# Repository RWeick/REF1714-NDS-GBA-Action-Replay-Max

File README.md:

# REF1714-NDS-GBA-Action-Replay-Max
A full schematic, optimized PCB, and the rom dump. Be sure to use SLA Resin if you print the cartridge connector.

PCB Thickness: 0.8 mm

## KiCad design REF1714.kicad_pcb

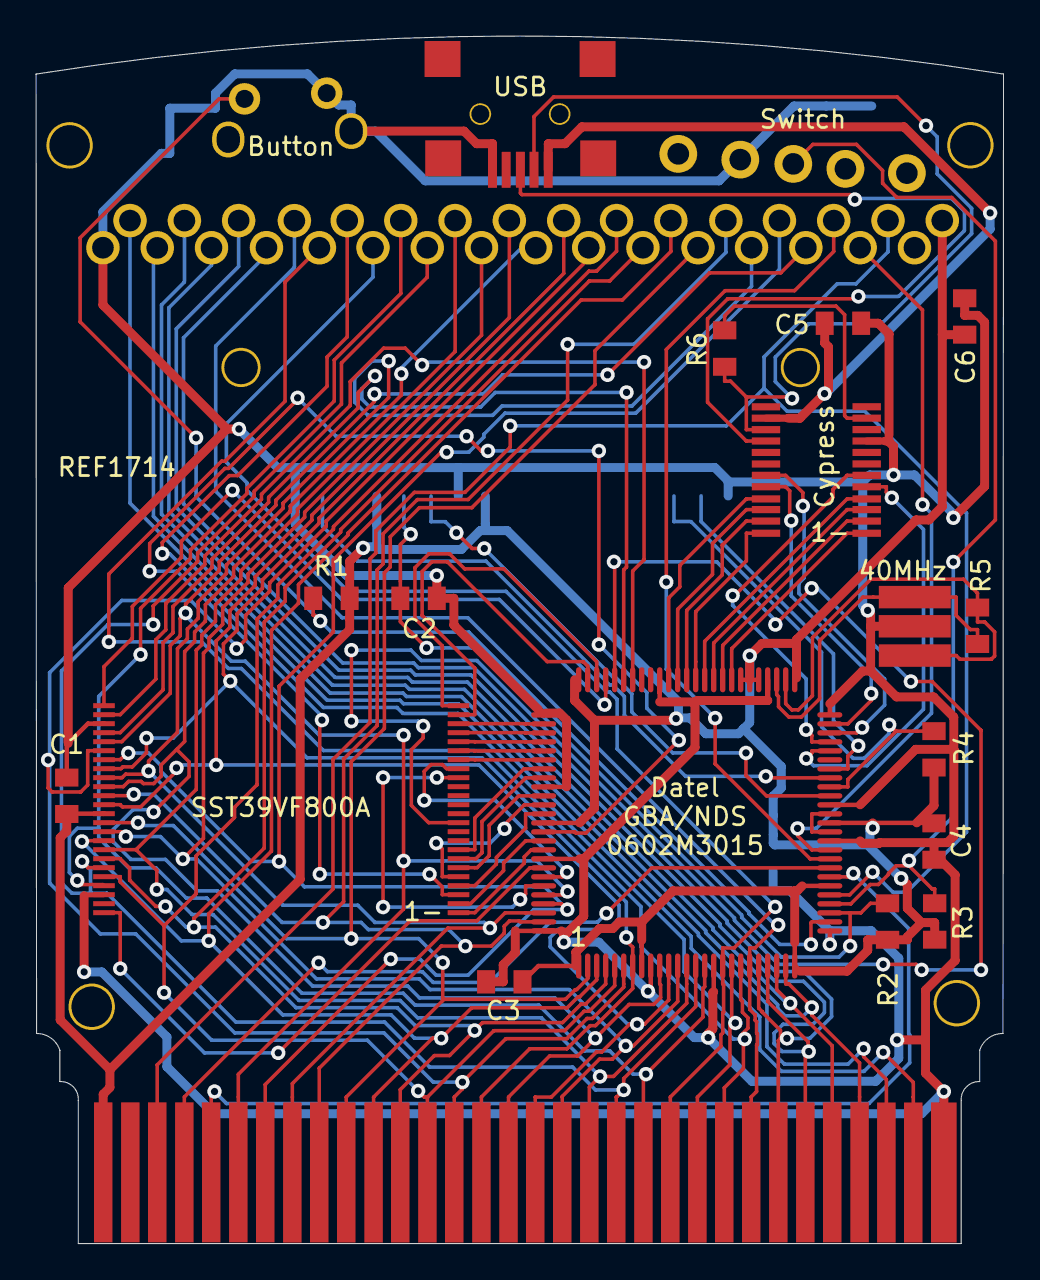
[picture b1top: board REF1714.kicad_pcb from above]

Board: 2 copper layers, 53.8 x 67.1 mm, 24 parts (0 on the bottom side), 81 nets.

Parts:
C1, C5: 400nF 0805; AR Max Capacitor
C2, C3, C4, C6: 100nF 0805; AR Max Capacitor
C7: Conn_01x03_Female; AR MAX Back Cap
DrillHoles: AR MAX Drill Holes
J1: USB_B_Mini; USB_Mini_B
J2: SW_DPDT_x2; Angled Switch
J3: System_Edge_Connector; Edge Connector
J4: Game_Edge_Connector; Cartridge Slot, GBC
R1, R2, R3: 10k Ohm 0805; AR Max Capacitor
R4: 2.2k Ohm 0805; AR Max Capacitor
R5: 220k Ohm 0805; AR Max Capacitor
R6: 1.5k Ohm 0805; AR Max Capacitor
SW1: SW_Push_Dual; Angled Button
U1: SST39VF800A; sst39vf800a-70-4c-eke
U2: Datel_GBA/NDS 0602M3015; GBA AR Max FPGA
U3: NDS_Cart_Slot; NDS Slot
U4: Cypress Unknown; AR Max Cypress
Y1: Crystal_GND3; 40MHz Crystal

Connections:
/40MHz.Pin1: R5.1, U2.52 (IO), Y1.1
/40MHz.Pin2: R5.2, U2.53 (IO), Y1.2
/A16: J3.22 (A16), J4.22 (A16), U2.17 (IO)
/A17: J3.23 (A17), J4.23 (A17), U2.18 (IO)
/A18: J3.24 (A18), J4.24 (A18), U2.19 (IO)
/A19: J3.25 (A19), J4.25 (A19), U2.20 (IO)
/A20: J3.26 (A20), J4.26 (A20), U2.21 (IO)
/A21: J3.27 (A21), J4.27 (A21), U2.22 (IO)
/A22: J3.28 (A22), J4.28 (A22), U2.23 (IO)
/A23: J3.29 (A23), J4.29 (A23), U2.24 (IO)
/AD0: J3.6 (AD0), J4.6 (AD0), U1.29 (DQ0), U2.96 (IO)
/AD1: J3.7 (AD1), J4.7 (AD1), U1.31 (DQ1), U2.97 (IO)
/AD2: J3.8 (AD2), J4.8 (AD2), U1.33 (DQ2), U2.98 (IO)
/AD3: J3.9 (AD3), J4.9 (AD3), U1.35 (DQ3), U2.99 (IO)
/AD4: J3.10 (AD4), J4.10 (AD4), U1.38 (DQ4), U2.2 (IO)
/AD5: J3.11 (AD5), J4.11 (AD5), U1.40 (DQ5), U2.3 (IO)
/AD6: J3.12 (AD6), J4.12 (AD6), U1.42 (DQ6), U2.4 (IO)
/AD7: J3.13 (AD7), J4.13 (AD7), U1.44 (DQ7), U2.5 (IO)
/AD8: J3.14 (AD8), J4.14 (AD8), U1.30 (DQ8), U2.6 (IO)
/AD9: J3.15 (AD9), J4.15 (AD9), U1.32 (DQ9), U2.7 (IO)
/AD10: J3.16 (AD10), J4.16 (AD10), U1.34 (DQ10), U2.10 (IO)
/AD11: J3.17 (AD11), J4.17 (AD11), U1.36 (DQ11), U2.11 (IO)
/AD12: J3.18 (AD12), J4.18 (AD12), U1.39 (DQ12), U2.12 (IO)
/AD13: J3.19 (AD13), J4.19 (AD13), U1.41 (DQ13), U2.13 (IO)
/AD14: J3.20 (AD14), J4.20 (AD14), U1.43 (DQ14), U2.14 (IO)
/AD15: J3.21 (AD15), J4.21 (AD15), U1.45 (DQ15), U2.15 (IO)
/Button: R1.1, SW1.2, U2.27 (IO)
/CS.Rom.Game: J4.5 (/CS.ROM), U2.34 (IO)
/CS.Rom.Sys: J3.5 (/CS.ROM), U2.32 (IO)
/CS.SRAM: J3.30 (/CS.SRAM), J4.30 (/CS.SRAM)
/CY.P0-1: U2.59 (IO), U4.2 (P0-1)
/Cy.D+: J1.3 (D+), U4.16 (D+/SCLK)
/Cy.D-: J1.2 (D-), R6.2, U4.15 (D-/SDATA)
/Cy.P0-0: U2.58 (IO), U4.1 (P0-0)
/Cy.P0-2: U2.60 (IO), U4.3 (P0-2)
/Cy.P0-3: U2.61 (IO), U4.4 (P0-3)
/Cy.P0-4: U2.62 (IO), U4.24 (P0-4)
/Cy.P0-5: U2.63 (IO), U4.23 (P0-5)
/Cy.P0-6: U2.64 (IO), U4.22 (P0-6)
/Cy.P0-7: U2.65 (IO), U4.21 (P0-7)
/Cy.P1-0: U2.46 (IO), U4.5 (P1-0)
/Cy.P1-1: U2.49 (IO), U4.20 (P1-1)
/Cy.P1-2: U2.47 (IO), U4.6 (P1-2)
/Cy.P1-3: U2.48 (IO), U4.19 (P1-3)
/Cy.VREG: R6.1, U4.11 (VREG/P2-0)
/GND: C1.1, C2.2, C3.1, C4.2, C5.2, C6.1, C7.1, J1.5 (GND), J2.1 (A), J3.32 (GND), J4.32 (GND), SW1.3, SW1.4, U1.27 (VSS_1), U1.46 (VSS_2), U2.9 (IO), U2.16 (IO), U2.26 (IO), U2.36 (IO), U2.40 (IO), U2.50 (IO), U2.54 (IO), U2.66 (IO), U2.76 (IO), U2.84 (IO), U2.92 (IO), U2.100 (IO), U3.1 (GND), U3.7 (IRQ), U3.17 (GND), U3.18 (Mounting_Bracket), U3.19 (Mounting_Bracket), U4.9 (VSS), Y1.3
/Loop: U2.37 (IO), U2.39 (IO)
/NDS.CS2: U2.41 (IO), U3.6 (CS2)
/NDS.Clk: U2.43 (IO), U3.2 (CLK)
/NDS.D6: R4.1, U2.42 (IO), U3.15 (D6)
/NDS.D7: U2.44 (IO), U3.16 (D7)
/NDS.Reset: C2.1, R2.1, U2.28 (IO), U3.5 (Reset)
/REQ: J3.31 (/REQ), J4.31 (/REQ)
/Rd_Game: J4.4 (/RD), U2.35 (IO)
/Rd_Sys: J3.4 (/RD), U2.33 (IO)
/SST.A0: U1.25 (A0), U2.72 (IO)
/SST.A1: U1.24 (A1), U2.73 (IO)
/SST.A2: U1.23 (A2), U2.74 (IO)
/SST.A3: U1.22 (A3), U2.77 (IO)
/SST.A4: U1.21 (A4), U2.78 (IO)
/SST.A5: U1.20 (A5), U2.79 (IO)
/SST.A6: U1.19 (A6), U2.80 (IO)
/SST.A7: U1.18 (A7), U2.81 (IO)
/SST.A8: U1.8 (A8), U2.82 (IO)
/SST.A9: U1.7 (A9), U2.83 (IO)
/SST.A10: U1.6 (A10), U2.85 (IO)
/SST.A11: U1.5 (A11), U2.86 (IO)
/SST.A12: U1.4 (A12), U2.87 (IO)
/SST.A13: U1.3 (A13), U2.89 (IO)
/SST.A14: U1.2 (A14), U2.90 (IO)
/SST.A15: U1.1 (A15), U2.91 (IO)
/SST.A16: U1.48 (A16), U2.93 (IO)
/SST.A17: U1.17 (A17), U2.94 (IO)
/SST.A18: U1.16 (A18), U2.95 (IO)
/SST.CE: U1.26 (CE#), U2.69 (IO)
/SST.OE: U1.28 (OE#), U2.70 (IO)
/SST.WE: U1.11 (WE#), U2.71 (IO)
/Switch: J2.2 (B), R3.1, U2.29 (IO)
/USB.VBUS: C5.1, J1.1 (VBUS), U4.14 (VCC)
/VCC: C1.2, C3.2, C4.1, C6.2, C7.2, C7.3, J3.1 (+3.3V/+5V), J4.1 (+3.3V/+5V), R1.2, R2.2, R3.2, R4.2, U1.37 (VDD), U2.1 (IO), U2.8 (IO), U2.25 (IO), U2.31 (IO), U2.38 (IO), U2.51 (IO), U2.55 (IO), U2.56 (IO), U2.57 (IO), U2.75 (IO), U2.88 (IO), U3.4 (CS1), U3.8 (VCC)
/Write: J3.3 (/WR), J4.3 (/WR), U2.30 (IO)
